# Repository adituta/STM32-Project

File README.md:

# STM32-Project
In this repository I will upload all the research and development of a personal project on STM32 platform.

Hello evryone!
Happy New Year!

I've started documenting about the core concepts that I really need to know in order to bring this project to reality.
I've done some research about the communication protocols needed in this project such as SPI, I2C and UART, usecases when I need them, advantages and disadvantages in using them.
The YouTube video that opened my eyes can be accessed at: https://www.youtube.com/watch?v=IjjZcnwkrAg&t=492s
The documents that dive deep into every protocol can be accessed via the links below:
- SPI: https://www.analog.com/media/en/analog-dialogue/volume-52/number-3/introduction-to-spi-interface.pdf
- I2C: https://www.ti.com/lit/an/slva704/slva704.pdf?ts=1710888631958
- UART: https://www.analog.com/media/en/analog-dialogue/volume-54/number-4/uart-a-hardware-communication-protocol.pdf

Also, during the weeks since creating this repository I researched the reasons why an RTOS is well suited in accomplishing certain tasks. An RTOS is absolutely necessary in managing critical tasks and fine grained processing that have as results adjusting real-time systems (adjusting the fuel-to-air ratio in internal combustion engines by on demand necesities of the driver and the road, keeping a thermal powerplant running by permanently keeping track of the boiler and turbine parameters (temperature, pressure, synchronization with the grid, coal supply, emergency situations).

Of course, I will not start to build my own powerplant or car and find use for the RTOS. This operating systems are really well fitted in probes that gather data from the environment (for civil or military applications). As the project name suggests, my project has to collect data from the nature, do some processing on it, extrat some valuable insight and then send it to the master.

During this holyday, I received a semester project at Digital Signal Processing Course in which I had to think about a problem in which I can apply concepts of Frecquency Analysis in order to solve it. I thought that an RTOS can sense the enemy forces advancing and can determine the direction of fire from the enemy. This can be achieved by having an array of microphonnes through which the support can triangulate the direction af attacking troops. In addition, with other sensors on board the support can determine the enemy's position more precisely.
- Link to the DSP homework: 

Another developing ways is to make a system that can caputure images from time to time and detect abnormalities. Also, an autofocus system can be done by adjusting the image around a point of interest (mechanically adjusting the lenses or sharpening the image digitally).

Also, I've watched a video on how to use the CubeMX and CubeIDE and I'll follow a course on getting used to the features and environment offered by the STM32 platform.

==========================================
D 001
Hello! I've had a great semester and a full one! I didn't have time to work on this project because I had other projects going on and a lot to study!

From now on I'll continue to write in romanian!

Am facut urmatoarele avansuri in ceea ce priveste proiectul!
Am inceput sa studiez cum functioneaza perifericele pe placa STM32 F4 si sa vad cum este mapata memoria. Am scris si un program in care aplind un led pe un breadborad in mai multe maniere. Prima data am scris un program in bucla care aprinde si stinge becul dupa 500ms. Lucrul acesta consuma timp de procesor si pauzele acelea inseamna, de fapt, timpi morti in care procesorul nu executa intructiuni. Am facut apoi si o comunicatie seriala UART prin care trimiteam mesaje catre terminalul de pe laptop deschis cu Putty atunci cand se aprindea LED-ul. Apoi am folosit intreruperile pentru a controla cand se aprinde si stinge becul. 
Programul pe care l-am facut este urmatorul:

/**
 ******************************************************************************
 * @file           : main.c
 * @author         : Auto-generated by STM32CubeIDE
 * @brief          : Main program body
 ******************************************************************************
 * @attention
 *
 * Copyright (c) 2026 STMicroelectronics.
 * All rights reserved.
 *
 * This software is licensed under terms that can be found in the LICENSE file
 * in the root directory of this software component.
 * If no LICENSE file comes with this software, it is provided AS-IS.
 *
 ******************************************************************************
 */

#include <stdint.h>
#include<string.h>

#if !defined(__SOFT_FP__) && defined(__ARM_FP)
  #warning "FPU is not initialized, but the project is compiling for an FPU. Please initialize the FPU before use."
#endif

// GPIO
#define RCC_AHB1ENR (*(volatile uint32_t *)0x40023830)

#define GPIOA_MODER (*(volatile uint32_t *)0x40020000)
#define GPIOA_ODR (*(volatile uint32_t *)0x40020014)

#define LED_PIN 1

// SysTick --- registrii din nucleul Cortex-M4
#define SYST_CSR (*(volatile uint32_t *)0xE000E010)
#define SYST_RVR (*(volatile uint32_t *)0xE000E014)
#define SYST_CVR (*(volatile uint32_t *)0xE000E018)

#define SYST_CSR_ENABLE (1<<0)
#define SYST_CSR_TICKINT (1<<1)
#define SYST_CSR_CLOCKSOURCE (1<<2)

volatile uint32_t tick_count = 0;

//trebuie sa definesc handlerul urmator cu exact numele asta
void SysTick_Handler(void){
	tick_count++;
}

static void systick_init(uint32_t reload_value){
	SYST_RVR = reload_value;
	SYST_CVR = 0;
	SYST_CSR = SYST_CSR_ENABLE | SYST_CSR_TICKINT |SYST_CSR_CLOCKSOURCE;
}

static void delay(volatile uint32_t count){
	while(count--){
		__asm__ volatile ("nop");
	}
}

// aici setez partea de comunicatie prin UART

/* RCC APB1 - pentru USART2 */
#define RCC_APB1ENR  (*(volatile uint32_t *)0x40023840)

/* GPIOA Alternate Function Low register (pini 0-7) */
#define GPIOA_AFRL   (*(volatile uint32_t *)0x40020020)

/* USART2 */
#define USART2_SR   (*(volatile uint32_t *)0x40004400)
#define USART2_DR   (*(volatile uint32_t *)0x40004404)
#define USART2_BRR  (*(volatile uint32_t *)0x40004408)
#define USART2_CR1  (*(volatile uint32_t *)0x4000440C)

#define USART_SR_TXE  (1 << 7)
#define USART_CR1_UE  (1 << 13)
#define USART_CR1_TE  (1 << 3)

static void uart2_init(void)
{
    /* activeaza ceasul pentru USART2 (bus APB1, bit 17) */
    RCC_APB1ENR |= (1 << 17);

    /* PA2 = TX, PA3 = RX -> mod Alternate Function (10) */
    GPIOA_MODER &= ~((0x3 << (2*2)) | (0x3 << (3*2)));
    GPIOA_MODER |=  ((0x2 << (2*2)) | (0x2 << (3*2)));

    /* AFRL: 4 biti per pin. PA2 -> biti 8-11, PA3 -> biti 12-15.
       AF7 = 0111 pentru USART2 */
    GPIOA_AFRL &= ~((0xF << (2*4)) | (0xF << (3*4)));
    GPIOA_AFRL |=  ((0x7 << (2*4)) | (0x7 << (3*4)));

    /* baud rate: 16MHz / 115200 ~= 139 */
    USART2_BRR = 139;

    /* activeaza USART + transmisie */
    USART2_CR1 = USART_CR1_UE | USART_CR1_TE;
}

static void uart2_send_char(char c)
{
    /* asteapta pana registrul de date e liber (TXE=1) */
    while (!(USART2_SR & USART_SR_TXE));
    USART2_DR = c;
}

static void uart2_send_string(const char *s)
{
    while (*s)
    {
        uart2_send_char(*s);
        s++;
    }
}

static void uint32_to_string(uint32_t nr, unsigned char* out){
	//zicem ca stringul are o dimensiune suficienta ca sa incapa datele pe el
	// trebuie sa extrag cifrele si sa le pun in string
	unsigned char buffer[20];

	int  i =0;
	while(nr!=0){
		buffer[i] = nr%10;
		i++;
		nr = nr/10;
	}

	// acum trebuie sa inversez numerele in buffer
	for(int j = 0;j<i/2;j++){
		//trebuie sa inversez ordinea lor
		unsigned char c = buffer[j];
		buffer[j] = buffer[i-1-j];
		buffer[i-1-j] = c;
	}

	//acum trebuie sa convertesc totul la ascii
	//trebuie sa am grija
	for(int j = 0;j<i;j++)
		buffer[j]+= '0';

	//facem un memcpy in bufferul de afisare
	//pun si caracterele null si endline
	buffer[i] = '\r';
	i++;
	buffer[i] = '\n';
	i++;
	buffer[i] = '\0';
	i++;
	memcpy(out, buffer, i);

}

int main(void)
{
	RCC_AHB1ENR |=(1<<0);

		GPIOA_MODER &= ~(0x3 <<(LED_PIN *2));
		GPIOA_MODER |= (0x1 <<(LED_PIN *2));

		systick_init(15999);

		uart2_init();
		uart2_send_string("UART OK\r\n");

		uint32_t last_toggle = 0;
			unsigned char nr_ascii[20];

			for(;;){
				if(tick_count - last_toggle >= 500){
					GPIOA_ODR ^= (1<<LED_PIN);
					last_toggle = tick_count;
					memset(nr_ascii, 0, 20);
					uint32_to_string(tick_count, nr_ascii);
					uart2_send_string("tick = ");
					uart2_send_string(nr_ascii);
				}
			}
}

==========================================

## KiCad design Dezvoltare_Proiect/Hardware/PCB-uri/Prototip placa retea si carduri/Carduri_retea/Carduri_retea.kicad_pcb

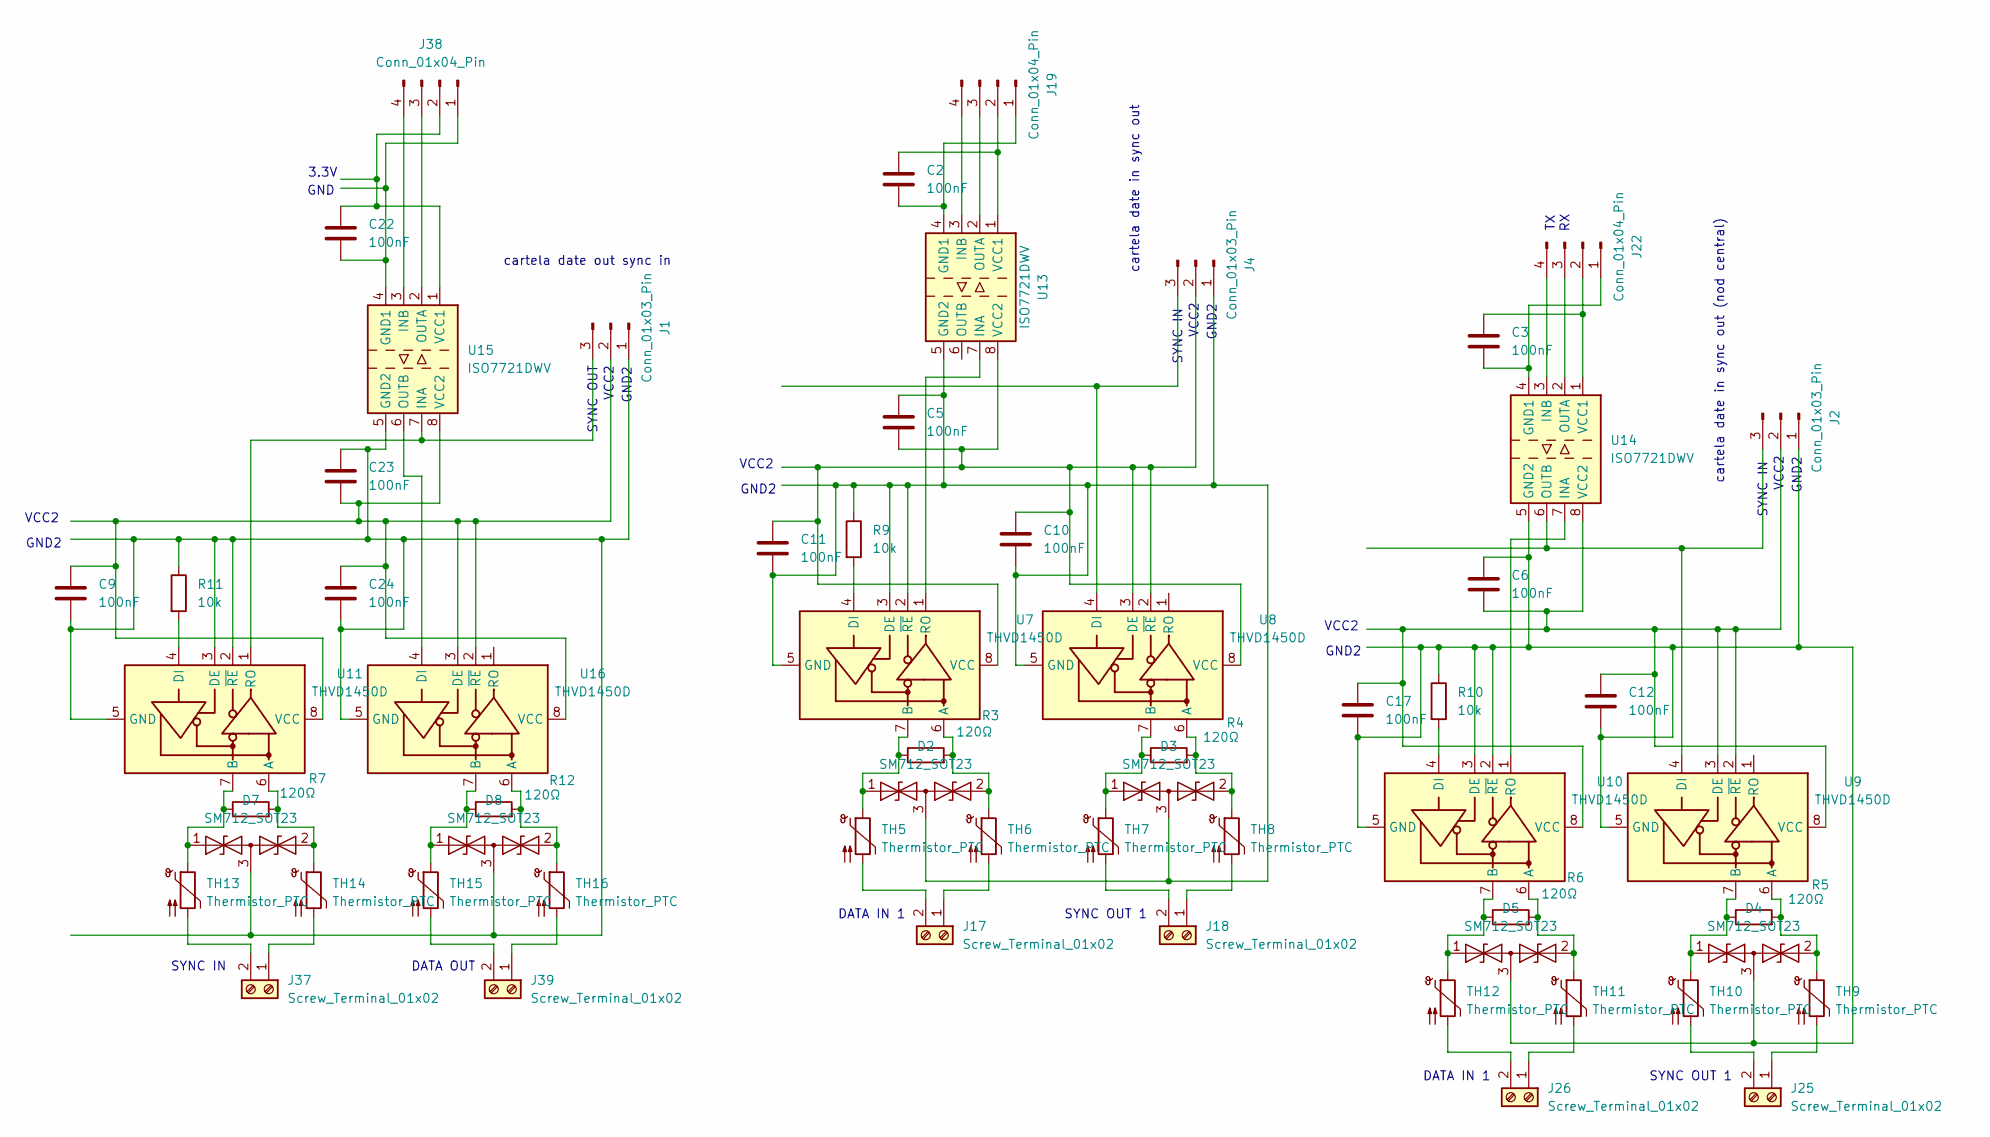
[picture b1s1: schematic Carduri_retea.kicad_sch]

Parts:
C2, C3, C5, C6, C9, C10, C11, C12, C17, C22, C23, C24: 100nF; C_0805_2012Metric
D2, D3, D4, D5, D7, D8: SM712_SOT23; SOT-23
J1, J2, J4: Conn_01x03_Pin; PinHeader_1x03_P2.54mm_Vertical
J17, J18, J25, J26, J37, J39: Screw_Terminal_01x02; TerminalBlock_MaiXu_MX126-5.0-02P_1x02_P5.00mm
J19, J22, J38: Conn_01x04_Pin; PinHeader_1x04_P2.54mm_Vertical
R3, R4, R5, R6, R7, R12: 120Ω; R_0805_2012Metric
R9, R10, R11: 10k; R_0805_2012Metric
TH5, TH6, TH7, TH8, TH9, TH10, TH11, TH12, TH13, TH14, TH15, TH16: Thermistor_PTC; R_0805_2012Metric
U7, U8, U9, U10, U11, U16: THVD1450D; SOIC-8_3.9x4.9mm_P1.27mm
U13, U14, U15: ISO7721DWV; SOIC-8_7.5x5.85mm_P1.27mm

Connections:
unnamed: D2.1 (A1), R3.1, TH5.1, U7.7 (B)
unnamed: D2.2 (A2), R3.2, TH6.1, U7.6 (A)
unnamed: C5.1, C10.2, C11.2, D2.3 (common), D3.3 (common), J4.1, R9.1, U7.2 (~RE), U7.3 (DE), U7.5 (GND), U8.5 (GND), U13.5 (GND2)
unnamed: D3.1 (A1), R4.1, TH7.1, U8.7 (B)
unnamed: D3.2 (A2), R4.2, TH8.1, U8.6 (A)
unnamed: D4.1 (A1), R5.1, TH10.1, U9.7 (B)
unnamed: D4.2 (A2), R5.2, TH9.1, U9.6 (A)
unnamed: C6.1, C12.2, C17.2, D4.3 (common), D5.3 (common), J2.1, R10.1, U9.5 (GND), U10.2 (~RE), U10.3 (DE), U10.5 (GND), U14.5 (GND2)
unnamed: D5.1 (A1), R6.1, TH12.1, U10.7 (B)
unnamed: D5.2 (A2), R6.2, TH11.1, U10.6 (A)
unnamed: D7.1 (A1), R7.1, TH13.1, U11.7 (B)
unnamed: D7.2 (A2), R7.2, TH14.1, U11.6 (A)
unnamed: C9.2, C23.1, C24.2, D7.3 (common), D8.3 (common), J1.1, R11.1, U11.2 (~RE), U11.3 (DE), U11.5 (GND), U15.5 (GND2), U16.5 (GND)
unnamed: D8.1 (A1), R12.1, TH15.1, U16.7 (B)
unnamed: D8.2 (A2), R12.2, TH16.1, U16.6 (A)
unnamed: C9.1, C23.2, C24.1, J1.2, U11.8 (VCC), U15.8 (VCC2), U16.2 (~RE), U16.3 (DE), U16.8 (VCC)
unnamed: J1.3, U11.1 (RO), U15.7 (INA)
unnamed: C6.2, C12.1, C17.1, J2.2, U9.2 (~RE), U9.3 (DE), U9.8 (VCC), U10.8 (VCC), U14.8 (VCC2)
unnamed: J2.3, U9.4 (DI), U14.6 (OUTB)
unnamed: C5.2, C10.1, C11.1, J4.2, U7.8 (VCC), U8.2 (~RE), U8.3 (DE), U8.8 (VCC), U13.8 (VCC2)
unnamed: J4.3, U8.4 (DI)
unnamed: J17.1, TH6.2
unnamed: J17.2, TH5.2
unnamed: J18.1, TH8.2
unnamed: J18.2, TH7.2
unnamed: C2.2, J19.1, U13.4 (GND1)
unnamed: C2.1, J19.2, U13.1 (VCC1)
unnamed: J19.3, U13.2 (OUTA)
unnamed: J19.4, U13.3 (INB)
unnamed: C3.2, J22.1, U14.4 (GND1)
unnamed: C3.1, J22.2, U14.1 (VCC1)
unnamed: J22.3, U14.2 (OUTA)
unnamed: J22.4, U14.3 (INB)
unnamed: J25.1, TH9.2
unnamed: J25.2, TH10.2
unnamed: J26.1, TH11.2
unnamed: J26.2, TH12.2
unnamed: J37.1, TH14.2
unnamed: J37.2, TH13.2
unnamed: C22.2, J38.1, U15.4 (GND1)
unnamed: C22.1, J38.2, U15.1 (VCC1)
unnamed: J38.3, U15.2 (OUTA)
unnamed: J38.4, U15.3 (INB)
unnamed: J39.1, TH16.2
unnamed: J39.2, TH15.2
unnamed: R9.2, U7.4 (DI)
unnamed: R10.2, U10.4 (DI)
unnamed: U10.1 (RO), U14.7 (INA)
unnamed: R11.2, U11.4 (DI)
unnamed: U7.1 (RO), U13.7 (INA)
unnamed: U15.6 (OUTB), U16.4 (DI)

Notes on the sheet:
GND2
VCC2
cartela date in sync out
GND
cartela date in sync out (nod central)
3.3V
SYNC IN
SYNC OUT 1
TX RX
SYNC OUT
DATA IN 1
VCC2
GND2
cartela date out sync in
DATA OUT

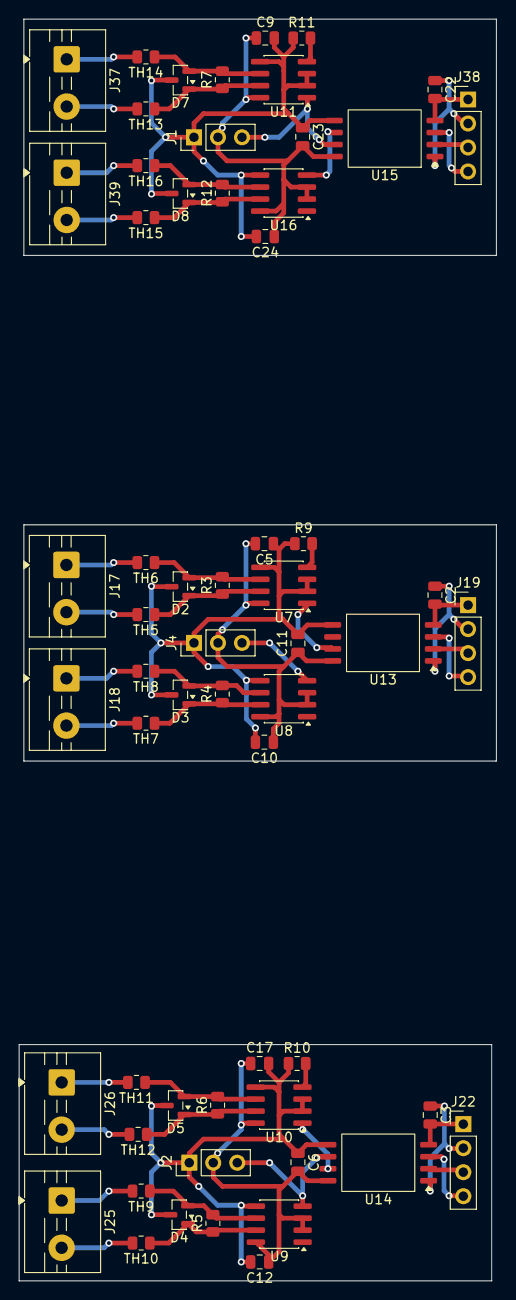
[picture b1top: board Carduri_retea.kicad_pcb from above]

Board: 2 copper layers, 50.5 x 133.5 mm, 60 parts (0 on the bottom side), 51 nets.

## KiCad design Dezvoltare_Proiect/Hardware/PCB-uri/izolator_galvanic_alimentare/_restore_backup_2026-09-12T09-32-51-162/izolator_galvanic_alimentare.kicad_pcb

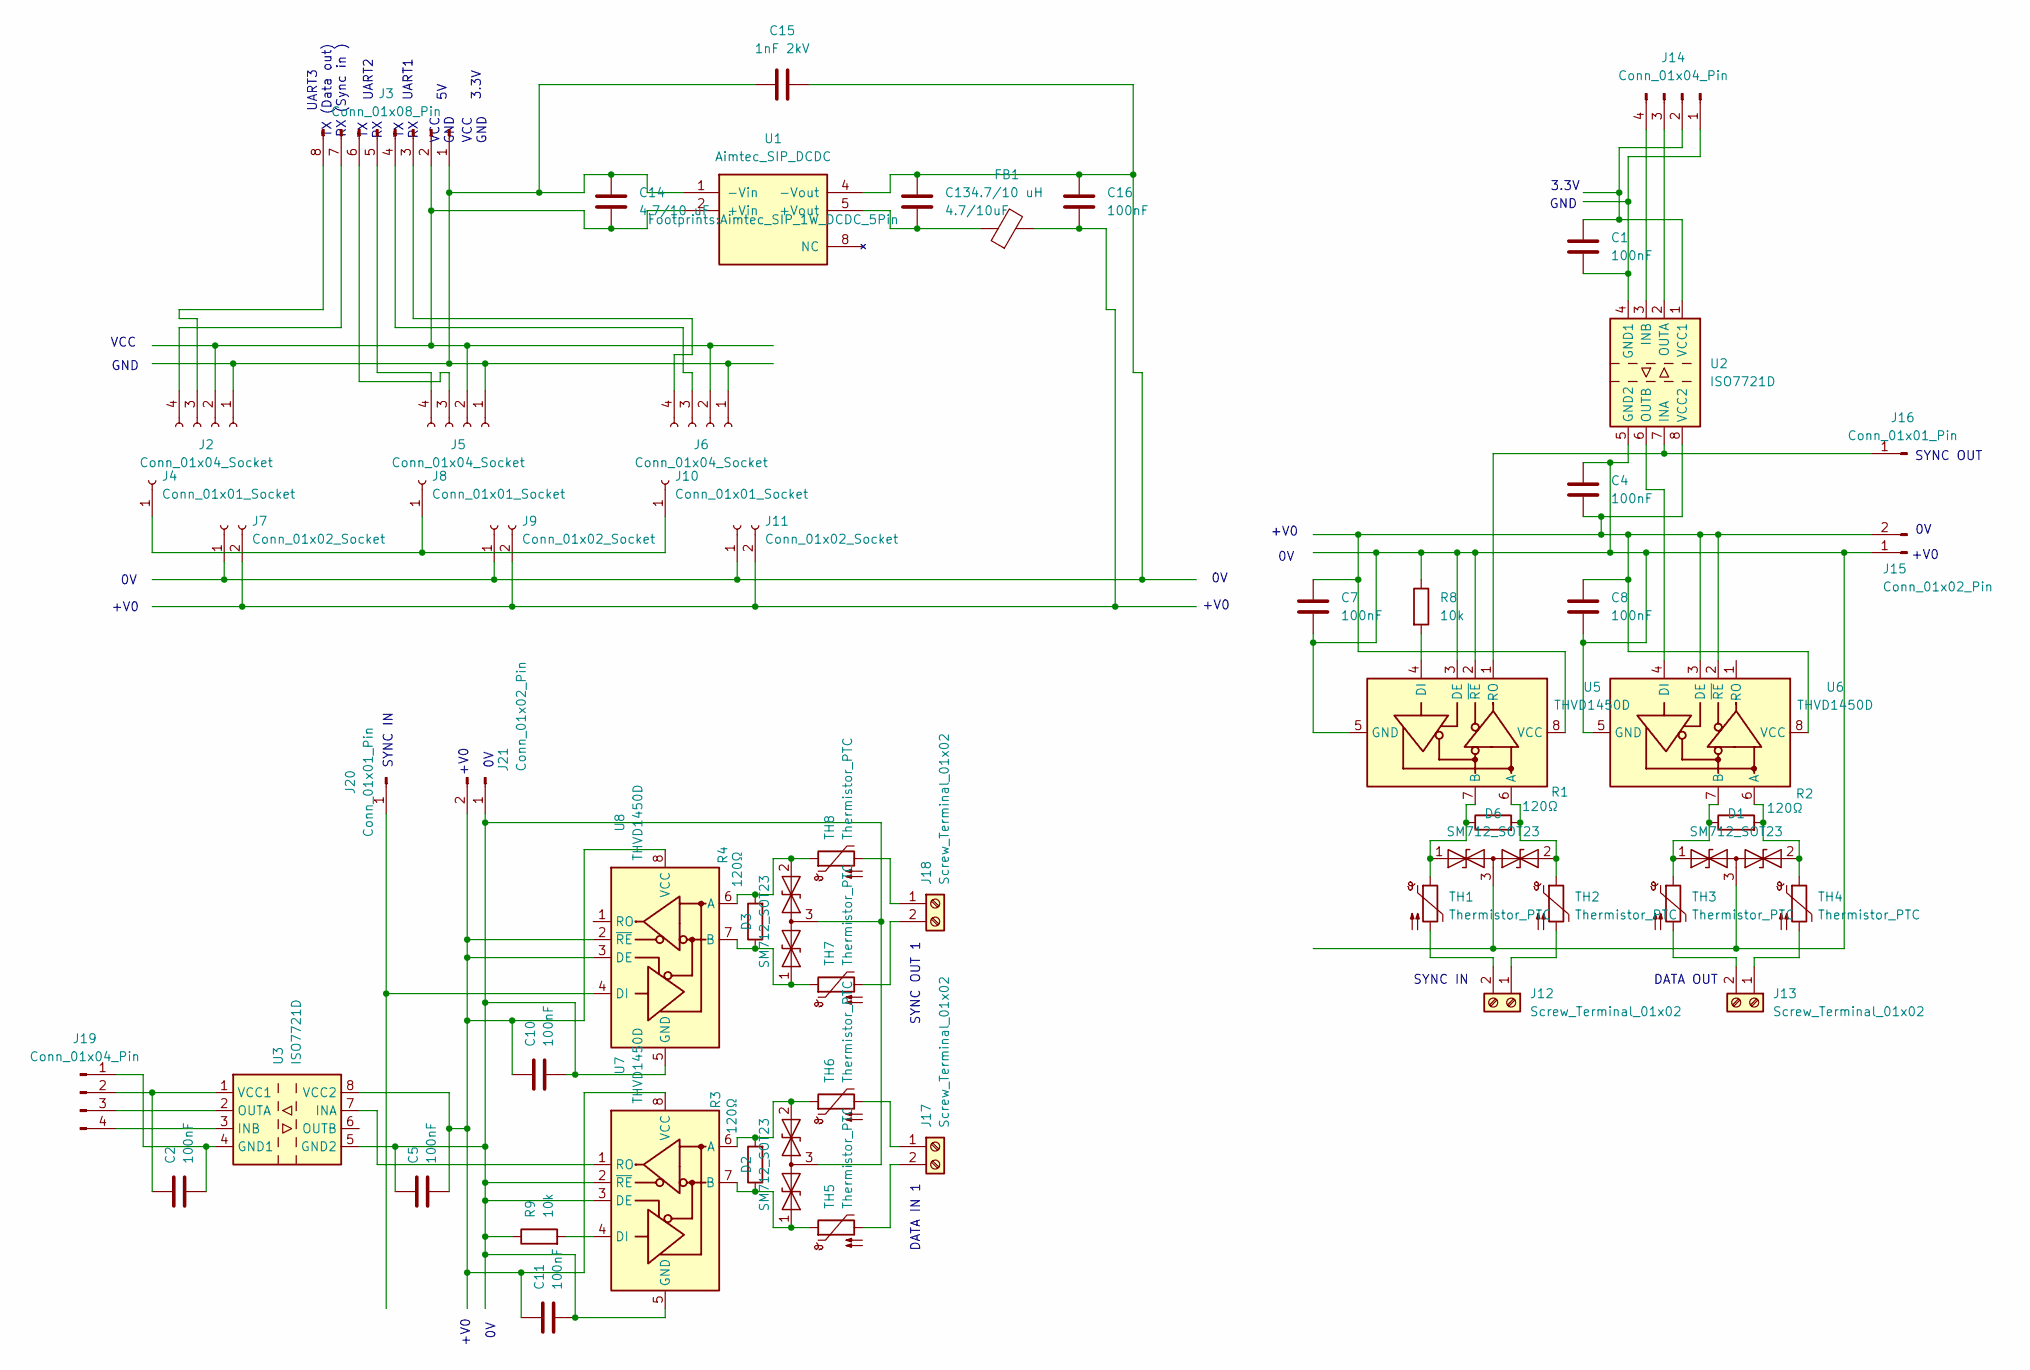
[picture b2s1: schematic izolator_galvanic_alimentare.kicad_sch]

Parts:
C1, C2, C4, C5, C7, C8, C10, C11, C16: 100nF; C_0805_2012Metric
C13: 4.7/10uF; C_0805_2012Metric
C14: 4.7/10 uF; C_0805_2012Metric
C15: 1nF 2kV; C_Disc_D8.0mm_W5.0mm_P7.50mm
D1, D2, D3, D6: SM712_SOT23; SOT-23
FB1: 4.7/10 uH; L_0805_2012Metric
J2, J5, J6: Conn_01x04_Socket; PinHeader_1x04_P2.54mm_Vertical
J3: Conn_01x08_Pin; PinHeader_1x08_P2.54mm_Vertical
J4, J8, J10: Conn_01x01_Socket; PinHeader_1x01_P2.54mm_Vertical
J7, J9, J11: Conn_01x02_Socket; PinHeader_1x02_P2.54mm_Vertical
J12, J13, J17, J18: Screw_Terminal_01x02; TerminalBlock_MaiXu_MX126-5.0-02P_1x02_P5.00mm
J14, J19: Conn_01x04_Pin; PinHeader_1x04_P2.54mm_Vertical
J15, J21: Conn_01x02_Pin; PinHeader_1x02_P2.54mm_Vertical
J16, J20: Conn_01x01_Pin; PinHeader_1x01_P2.54mm_Vertical
R1, R2, R3, R4: 120Ω; R_0805_2012Metric
R8, R9: 10k; R_0805_2012Metric
TH1, TH2, TH3, TH4, TH5, TH6, TH7, TH8: Thermistor_PTC; R_0805_2012Metric
U1: Aimtec_SIP_DCDC; Aimtec_SIP_1W_DCDC_5Pin
U2, U3: ISO7721D; SOIC-8_3.9x4.9mm_P1.27mm
U5, U6, U7, U8: THVD1450D; SOIC-8_3.9x4.9mm_P1.27mm

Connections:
unnamed: D1.1 (A1), R2.1, TH3.1, U6.7 (B)
unnamed: D1.2 (A2), R2.2, TH4.1, U6.6 (A)
unnamed: C4.1, C7.2, C8.2, D1.3 (common), D6.3 (common), J15.1, R8.1, U2.5 (GND2), U5.2 (~RE), U5.3 (DE), U5.5 (GND), U6.5 (GND)
unnamed: D2.1 (A1), R3.1, TH5.1, U7.7 (B)
unnamed: D2.2 (A2), R3.2, TH6.1, U7.6 (A)
unnamed: C5.1, C10.2, C11.2, D2.3 (common), D3.3 (common), J21.1, R9.1, U3.5 (GND2), U7.2 (~RE), U7.3 (DE), U7.5 (GND), U8.5 (GND)
unnamed: D3.1 (A1), R4.1, TH7.1, U8.7 (B)
unnamed: D3.2 (A2), R4.2, TH8.1, U8.6 (A)
unnamed: D6.1 (A1), R1.1, TH1.1, U5.7 (B)
unnamed: D6.2 (A2), R1.2, TH2.1, U5.6 (A)
unnamed: C14.2, C15.2, J2.1, J3.1, J5.1, J6.1, U1.1 (-Vin)
unnamed: C14.1, J2.2, J3.2, J5.2, J6.2, U1.2 (+Vin)
unnamed: J2.3, J3.8
unnamed: J2.4, J3.7
unnamed: J3.3, J6.4
unnamed: J3.4, J6.3
unnamed: J3.5, J5.4
unnamed: J3.6, J5.3
unnamed: J4.1 (Pin_1_1), J8.1 (Pin_1_1), J10.1 (Pin_1_1)
unnamed: J12.1, TH2.2
unnamed: J12.2, TH1.2
unnamed: J13.1, TH4.2
unnamed: J13.2, TH3.2
unnamed: C1.2, J14.1, U2.4 (GND1)
unnamed: C1.1, J14.2, U2.1 (VCC1)
unnamed: J14.3, U2.2 (OUTA)
unnamed: J14.4, U2.3 (INB)
unnamed: C4.2, C7.1, C8.1, J15.2, U2.8 (VCC2), U5.8 (VCC), U6.2 (~RE), U6.3 (DE), U6.8 (VCC)
unnamed: J16.1 (Pin_1_1), U2.7 (INA), U5.1 (RO)
unnamed: J17.1, TH6.2
unnamed: J17.2, TH5.2
unnamed: J18.1, TH8.2
unnamed: J18.2, TH7.2
unnamed: C2.2, J19.1, U3.4 (GND1)
unnamed: C2.1, J19.2, U3.1 (VCC1)
unnamed: J19.3, U3.2 (OUTA)
unnamed: J19.4, U3.3 (INB)
unnamed: J20.1 (Pin_1_1), U8.4 (DI)
unnamed: C5.2, C10.1, C11.1, J21.2, U3.8 (VCC2), U7.8 (VCC), U8.2 (~RE), U8.3 (DE), U8.8 (VCC)
unnamed: C13.1, FB1.1, U1.5 (+Vout)
unnamed: U2.6 (OUTB), U6.4 (DI)
unnamed: U3.7 (INA), U7.1 (RO)
unnamed: R8.2, U5.4 (DI)
unnamed: R9.2, U7.4 (DI)

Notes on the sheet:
UART1
SYNC IN
TX RX
VCC GND
+V0
SYNC OUT
3.3V
GND
VCC
+V0
DATA OUT
DATA IN 1
SYNC OUT 1
UART3 TX (Data out) RX (Sync in )
UART2
SYNC IN

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
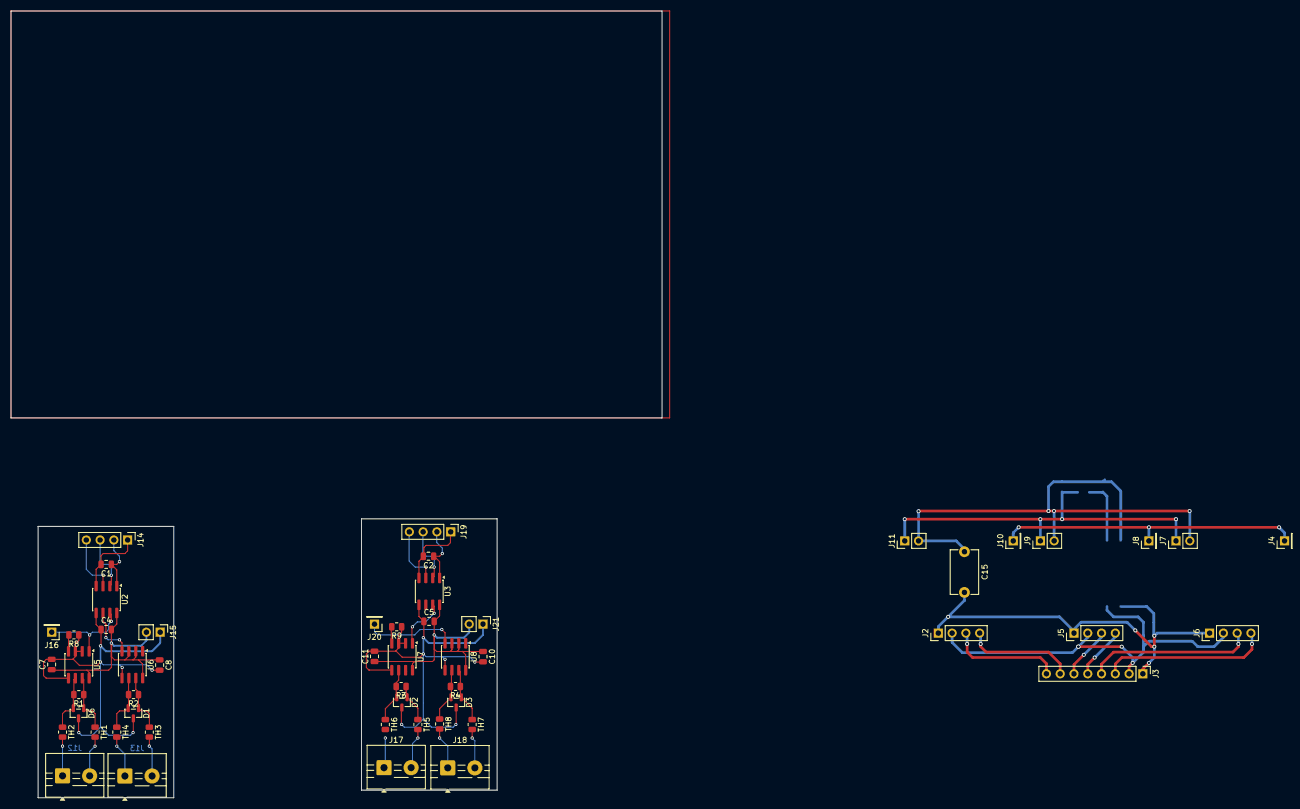
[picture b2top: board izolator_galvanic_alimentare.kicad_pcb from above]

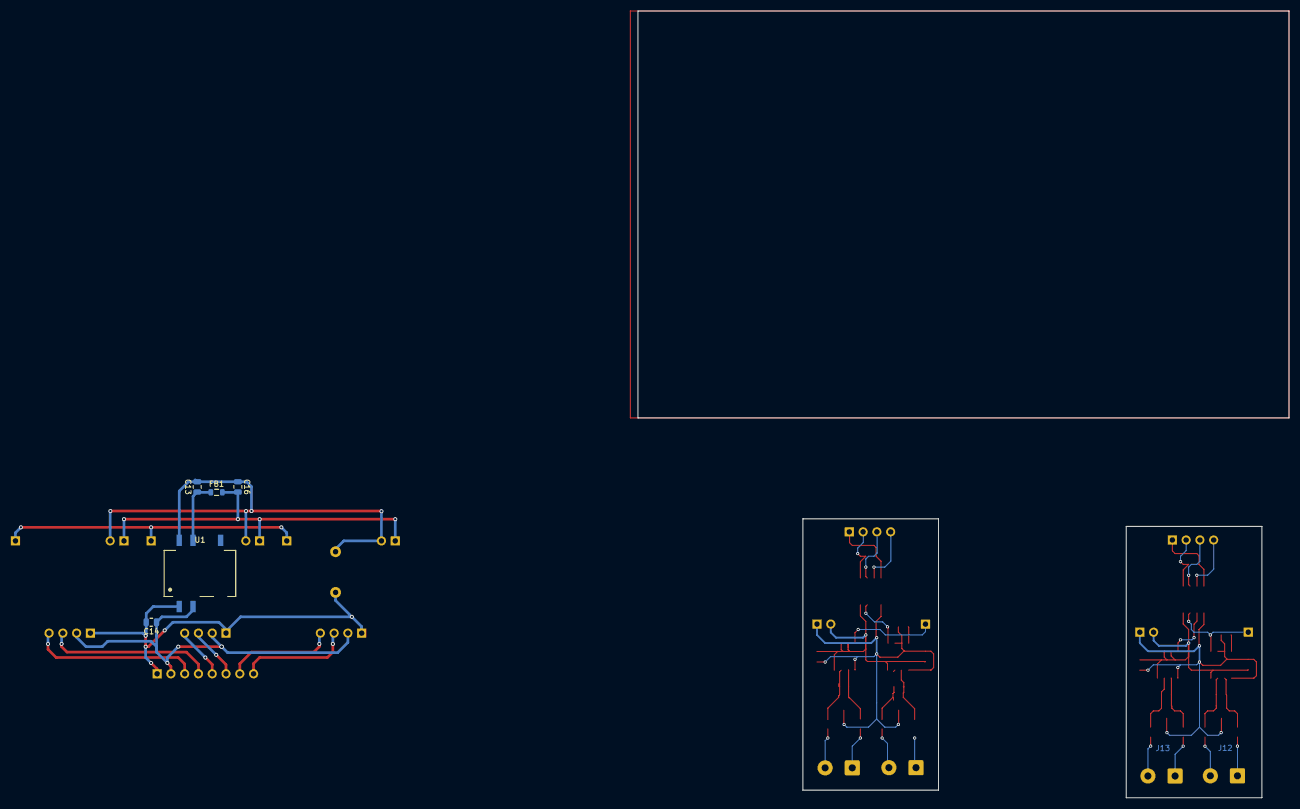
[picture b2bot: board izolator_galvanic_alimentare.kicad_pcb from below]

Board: 2 copper layers, 120.0 x 145.0 mm, 58 parts (5 on the bottom side), 46 nets.

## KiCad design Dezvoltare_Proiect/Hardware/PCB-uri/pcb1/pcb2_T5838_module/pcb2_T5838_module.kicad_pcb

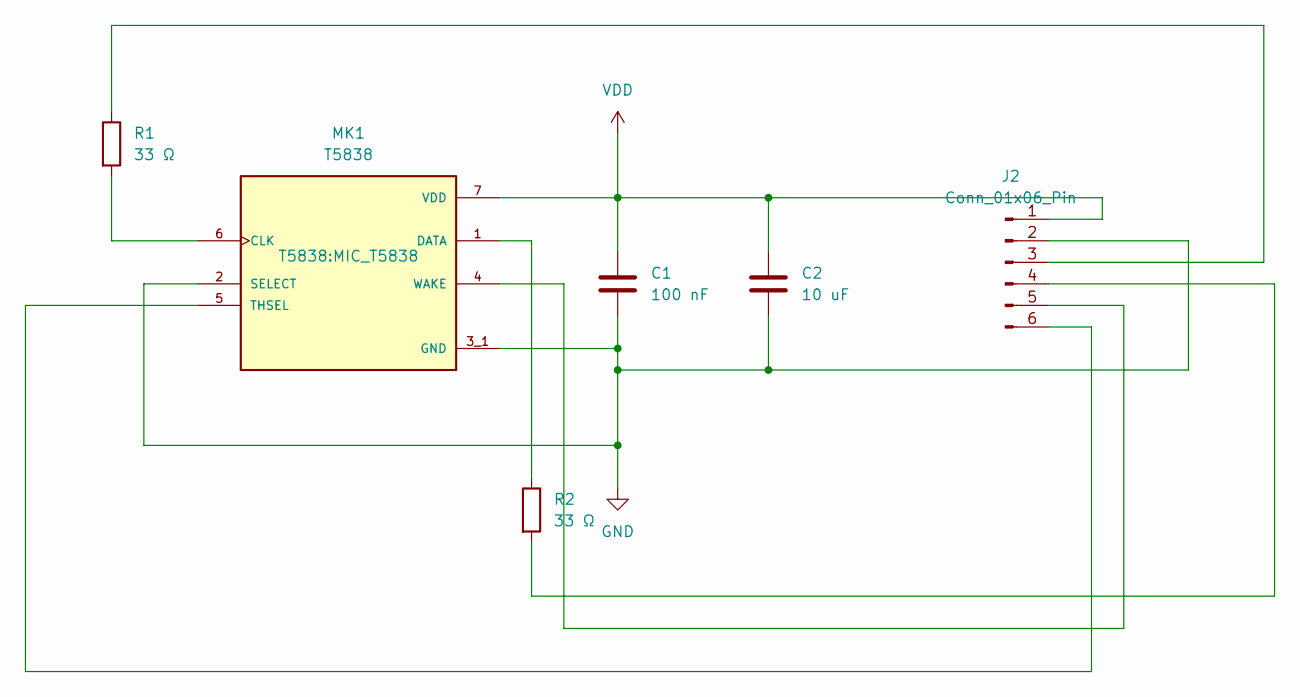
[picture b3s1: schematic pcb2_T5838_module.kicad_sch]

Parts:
C1: 100 nF; C_0805_2012Metric
C2: 10 uF; C_0805_2012Metric
J2: Conn_01x06_Pin; PinHeader_1x06_P2.54mm_Vertical
MK1: T5838; MIC_T5838; PARTREV 1.1
R1, R2: 33 Ω; R_0805_2012Metric

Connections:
GND: C1.2, C2.2, J2.2, MK1.2 (SELECT), MK1.3_1 (GND), MK1.3_2 (GND)
unnamed: J2.3, R1.1
unnamed: J2.4, R2.2
unnamed: J2.5, MK1.4 (WAKE)
unnamed: J2.6, MK1.5 (THSEL)
unnamed: MK1.6 (CLK), R1.2
unnamed: MK1.1 (DATA), R2.1
VDD: C1.1, C2.1, J2.1, MK1.7 (VDD)

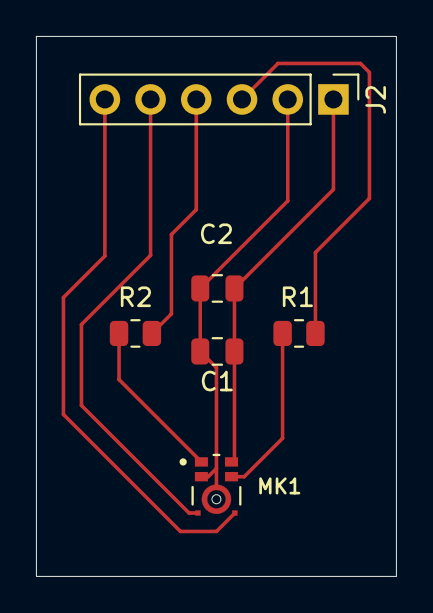
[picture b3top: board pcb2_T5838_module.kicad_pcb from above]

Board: 2 copper layers, 20.0 x 30.0 mm, 6 parts (0 on the bottom side), 8 nets.

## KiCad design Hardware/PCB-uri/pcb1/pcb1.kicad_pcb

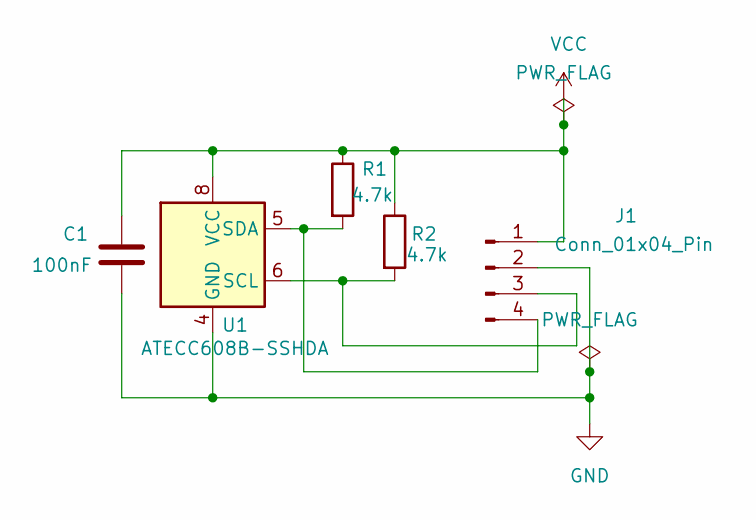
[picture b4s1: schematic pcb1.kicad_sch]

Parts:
C1: 100nF; C_0805_2012Metric
J1: Conn_01x04_Pin; PinHeader_1x04_P2.54mm_Vertical
R1, R2: 4.7k; R_0805_2012Metric
U1: ATECC608B-SSHDA; SOIC-8_3.9x4.9mm_P1.27mm

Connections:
GND: C1.2, J1.2, U1.4 (GND)
unnamed: J1.3, R2.2, U1.6 (SCL)
unnamed: J1.4, R1.2, U1.5 (SDA)
VCC: C1.1, J1.1, R1.1, R2.1, U1.8 (VCC)

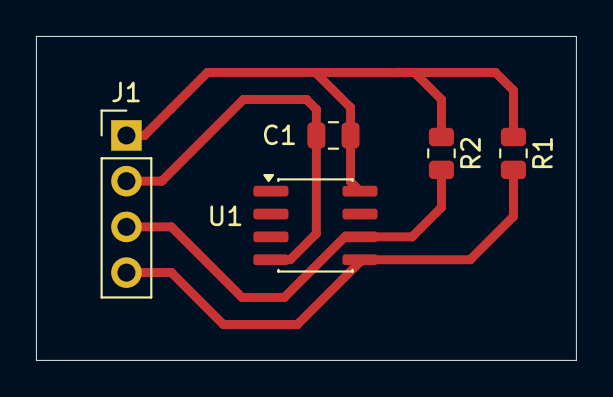
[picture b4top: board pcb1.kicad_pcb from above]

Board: 2 copper layers, 30.0 x 18.0 mm, 5 parts (0 on the bottom side), 4 nets.

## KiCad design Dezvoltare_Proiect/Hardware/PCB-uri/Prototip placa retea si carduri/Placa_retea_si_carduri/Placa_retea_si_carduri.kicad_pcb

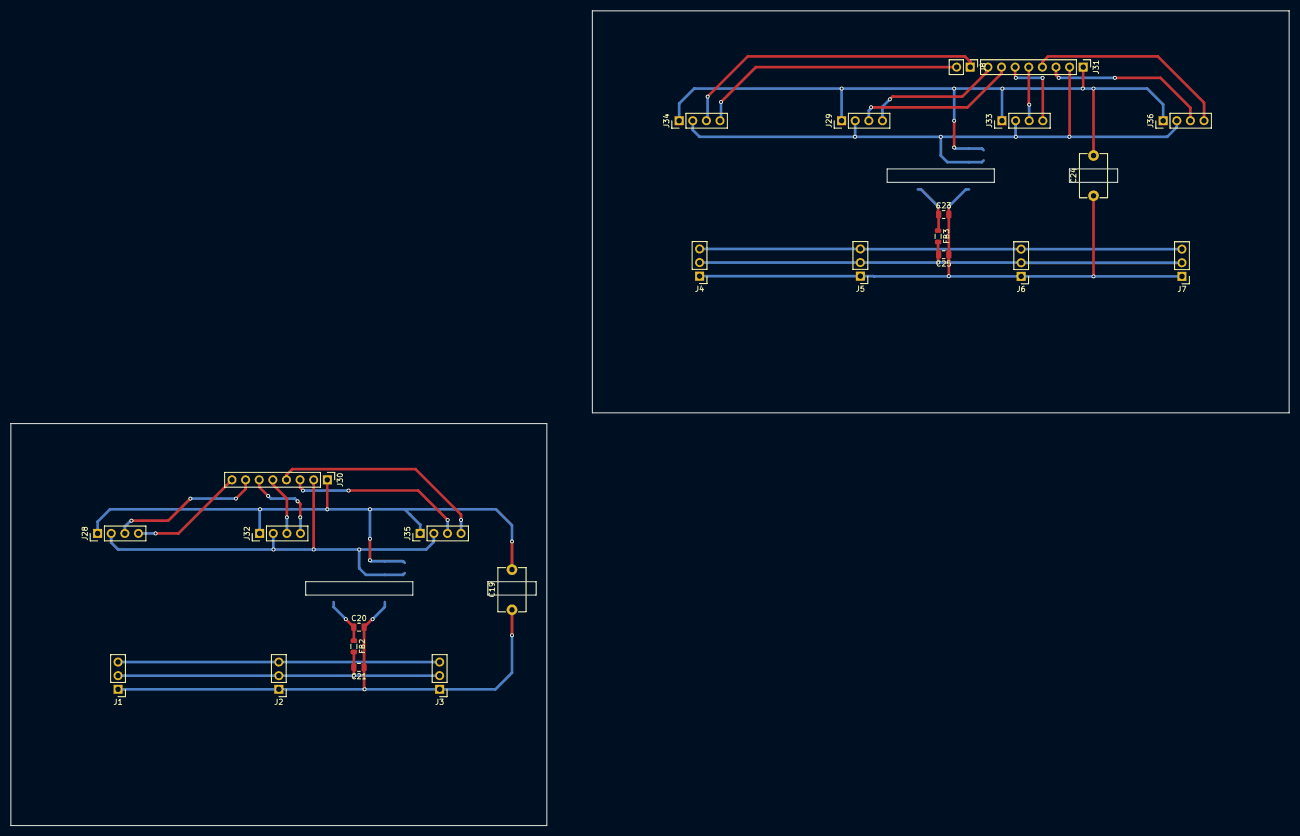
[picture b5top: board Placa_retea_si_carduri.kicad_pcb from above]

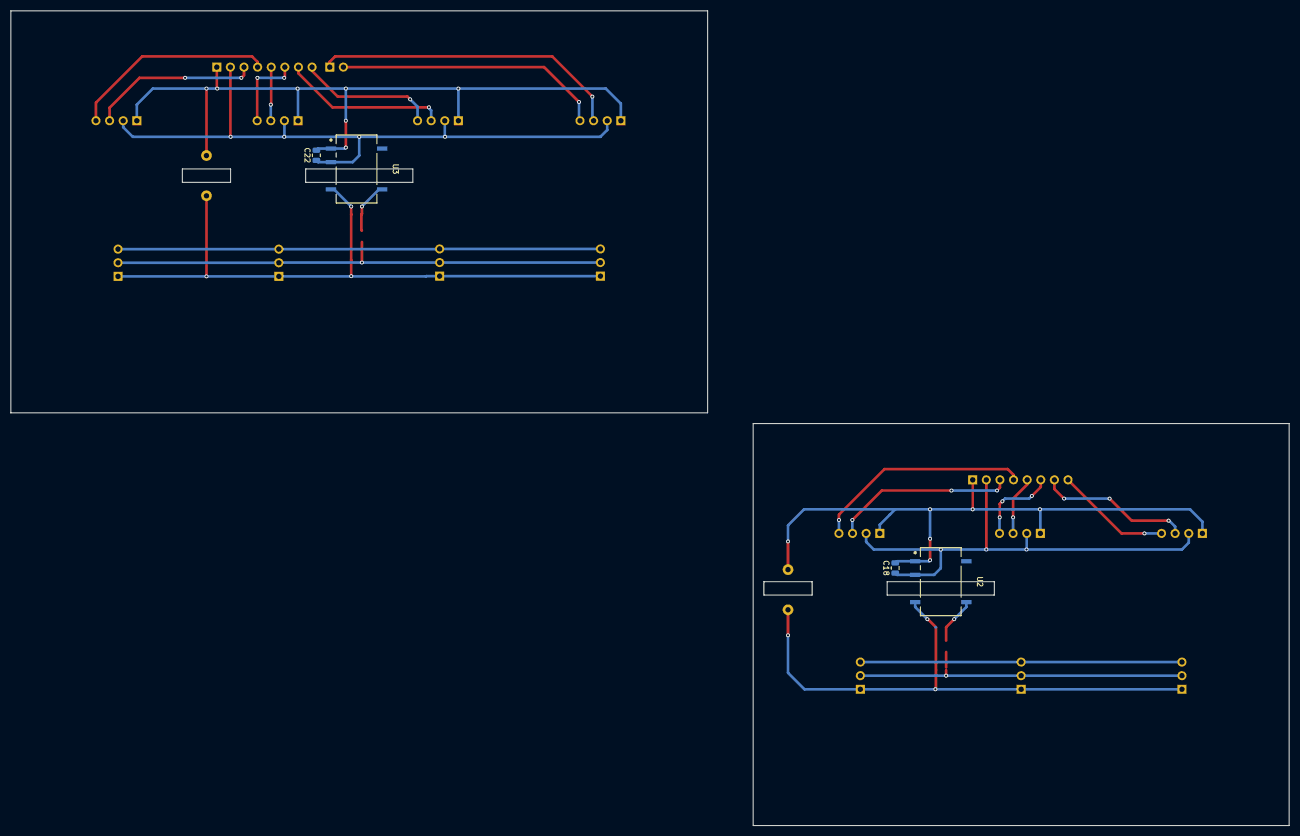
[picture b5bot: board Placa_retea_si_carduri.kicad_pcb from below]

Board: 2 copper layers, 238.5 x 152.0 mm, 29 parts (4 on the bottom side), 26 nets.

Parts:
C18, C22: 4.7/10 uF; C_0805_2012Metric
C19, C24: 1nF 2kV; C_Disc_D8.0mm_W5.0mm_P7.50mm
C20, C23: 4.7/10uF; C_0805_2012Metric
C21, C25: 100nF; C_0805_2012Metric
FB2, FB3: 4.7/10 uH; L_0805_2012Metric
J1, J2, J3, J4, J5, J6, J7: Conn_01x03_Socket; PinHeader_1x03_P2.54mm_Vertical
J8: Conn_01x02_Pin; PinHeader_1x02_P2.54mm_Vertical
J28, J29, J32, J33, J34, J35, J36: Conn_01x04_Socket; PinHeader_1x04_P2.54mm_Vertical
J30, J31: Conn_01x08_Pin; PinHeader_1x08_P2.54mm_Vertical
U2, U3: 1769405141; Wurth_1769405141_SMT-8

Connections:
unnamed: C19.1, C20.2, C21.1, J1.1, J2.1, J3.1, U2.4 (-VOUT)
unnamed: C21.2, FB2.2, J1.2, J2.2, J3.2
unnamed: J1.3, J2.3, J3.3
unnamed: C23.2, C24.1, C25.1, J4.1, J5.1, J6.1, J7.1, U3.4 (-VOUT)
unnamed: C25.2, FB3.2, J4.2, J5.2, J6.2, J7.2
unnamed: J4.3, J5.3, J6.3, J7.3
unnamed: C18.2, C19.2, J28.1, J30.1, J32.1, J35.1, U2.1 (-VIN)
unnamed: C18.1, J28.2, J30.2, J32.2, J35.2, U2.2 (+VIN)
unnamed: J28.3, J30.7
unnamed: J28.4, J30.8
unnamed: C22.2, C24.2, J29.1, J31.1, J33.1, J34.1, J36.1, U3.1 (-VIN)
unnamed: C22.1, J29.2, J31.2, J33.2, J34.2, J36.2, U3.2 (+VIN)
unnamed: J29.3, J31.7
unnamed: J29.4, J31.8
unnamed: J30.3, J35.3
unnamed: J30.4, J35.4
unnamed: J30.5, J32.3
unnamed: J30.6, J32.4
unnamed: J31.3, J36.3
unnamed: J31.4, J36.4
unnamed: J31.5, J33.3
unnamed: J31.6, J33.4
unnamed: J8.1, J34.3
unnamed: J8.2, J34.4
unnamed: C20.1, FB2.1, U2.5 (+VOUT)
unnamed: C23.1, FB3.1, U3.5 (+VOUT)

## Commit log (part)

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2025-12-11 Rename project title from 'Proiect-STM32' to 'STM32-Project'
2026-01-02 Update README with project details and resources
    Added introductory content and resources for STM32 project.
2026-01-02 Fix typo in New Year greeting
2026-01-02 Enhance README with RTOS and project insights
    Expanded the README with insights on RTOS applications and semester project ideas related to Digital Signal Processing.
2026-01-02 Update README with project details and corrections
    Corrected typos and improved clarity in the project description.
2026-06-15 Update README with project progress and STM32 details
    Added detailed project updates and STM32 programming notes in Romanian.
